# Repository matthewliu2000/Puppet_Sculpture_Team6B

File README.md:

# Puppet_Sculpture_Team6B
github repository for Team 6B ECE3872 Sculpture Project

# Hardware
1. PCB Schematic (shield_schematic.sh)
2. shield_schematic.brd
3. PCB Eagle Files: ECE3872A_6B_PCB_Shield.zip

# Software
1. HW & SW Component Level Tests: in test_code Folder
2. Draft Simulation Code: ArduinoSimulationCode.ino
3. Final Simulation Code: ArduinoSimulationCodeV2.ino

# Final Demonstration: 
https://youtu.be/2q0zukCzHsM

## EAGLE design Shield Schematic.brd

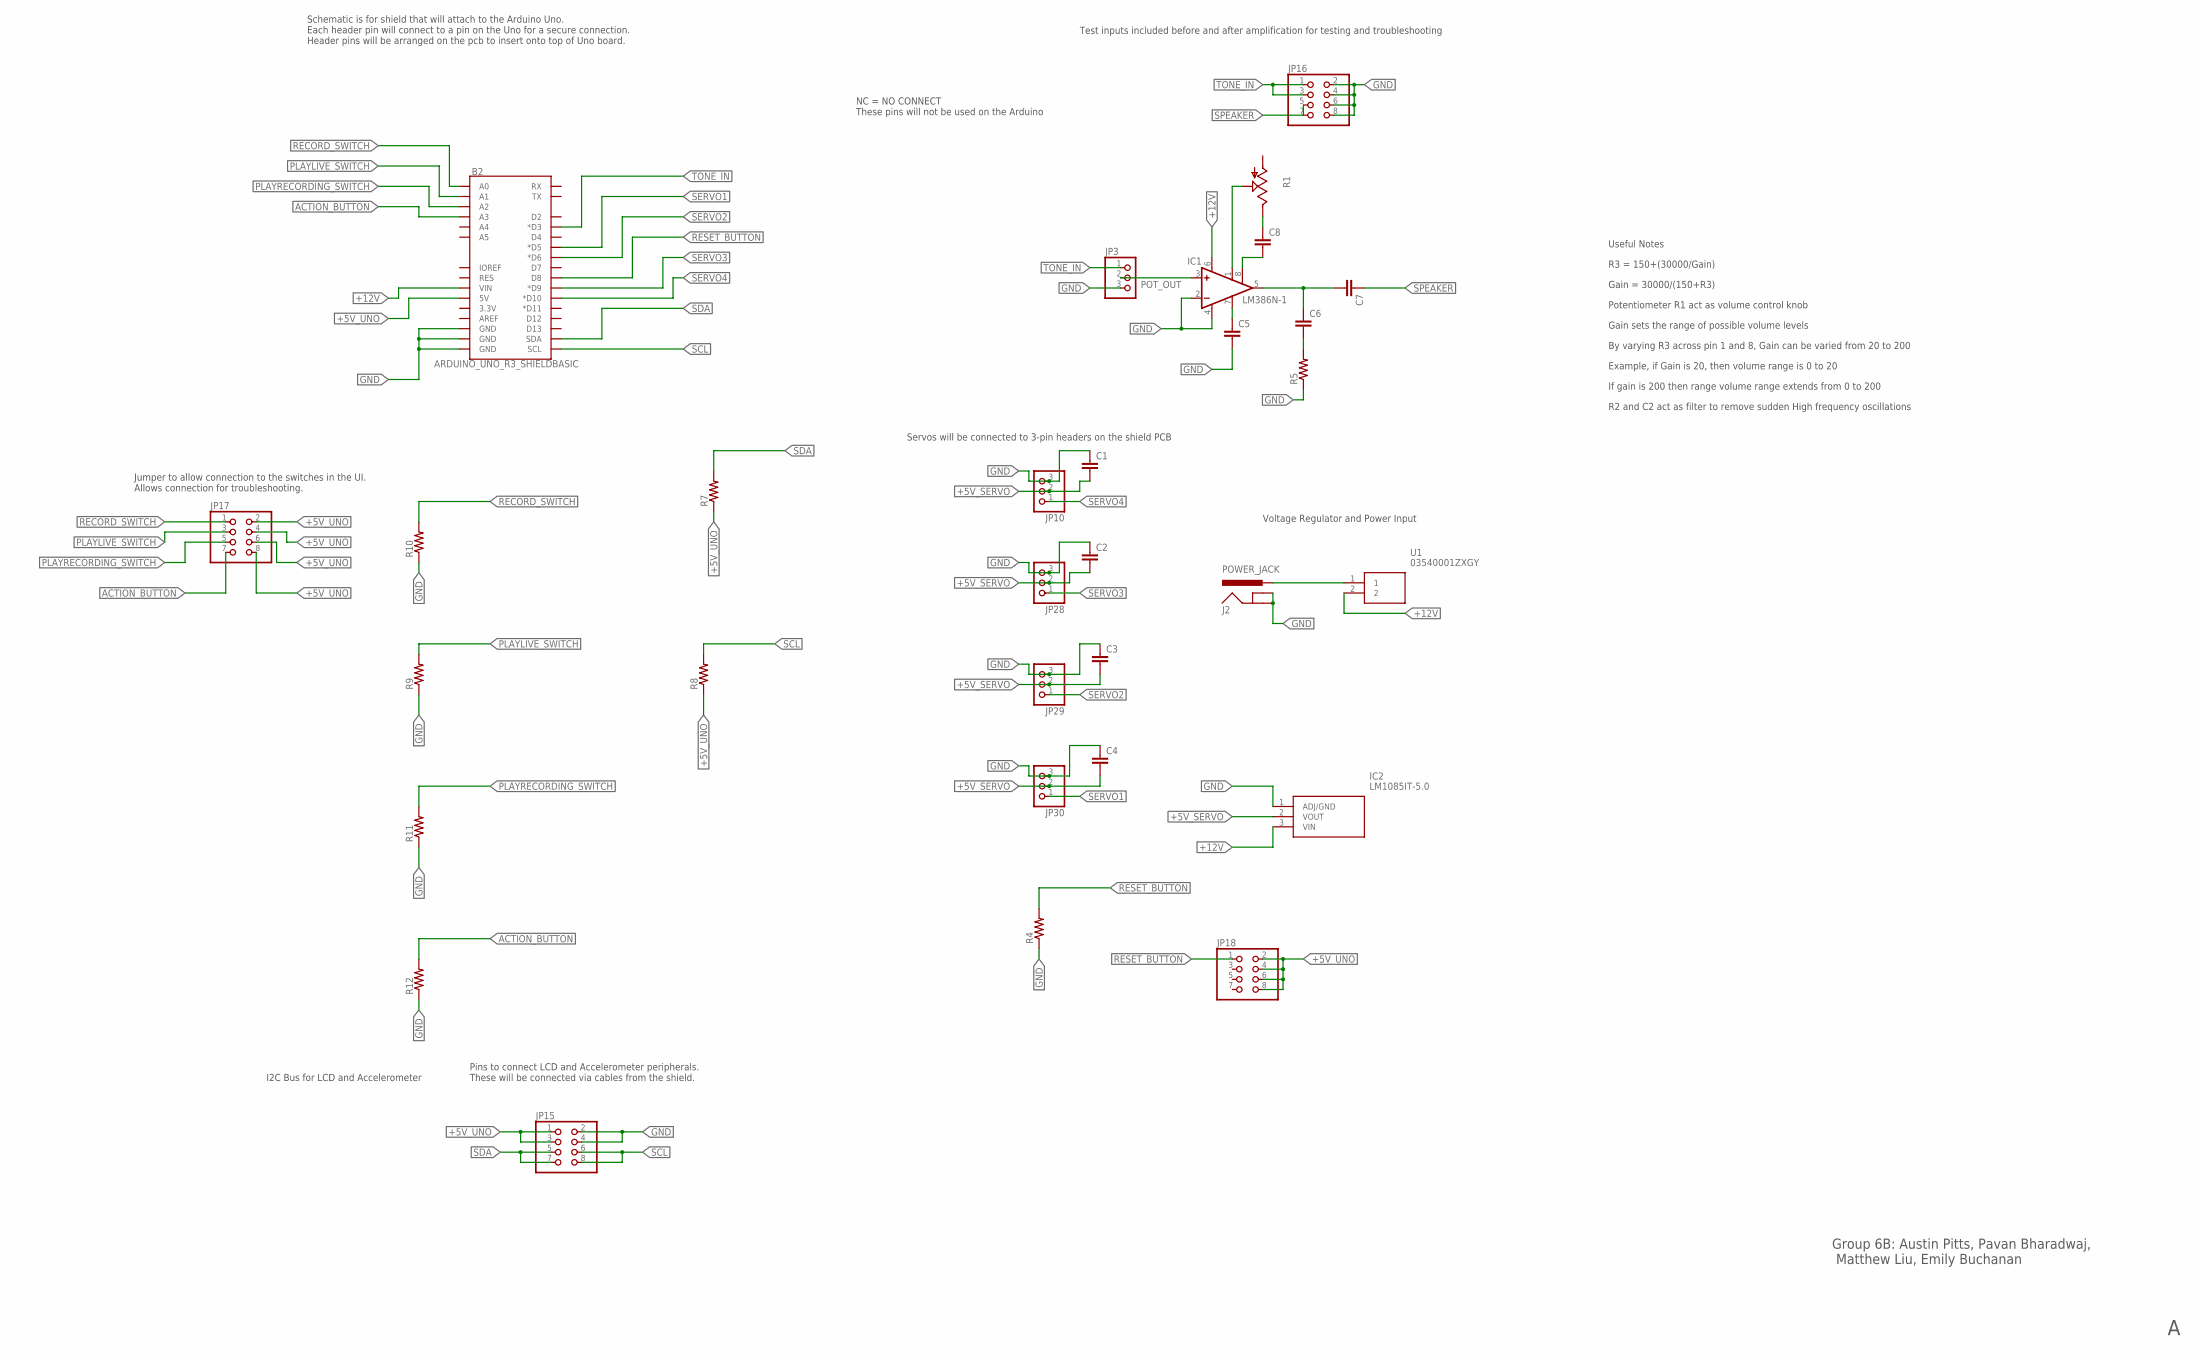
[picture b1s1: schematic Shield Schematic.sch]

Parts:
B2: ARDUINO_UNO_R3_SHIELDBASIC; UNO_R3_SHIELD
C1, C2, C3, C4, C5, C6, C7, C8: C2,5-3; C2.5-3
IC1: LM386N-1; DIL08
IC2: LM1085IT-5.0; TO254P470X1016X2222-3P
J2: POWER_JACK; POWER_JACK_PTH
JP3, JP10, JP28, JP29, JP30: PINHD-1X3; 1X03
JP15, JP16, JP17, JP18: PINHD-2X4; 2X04
R1: TRIM_US-B25P; B25P
R4, R5, R7, R8, R9, R10, R11, R12: R-US_0207/7; 0207/7
U1: 03540001ZXGY; 03540101ZXGY

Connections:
+5V_SERVO: C1.2, C2.2, C3.2, C4.2, IC2.2 (VOUT), JP10.2, JP28.2, JP29.2, JP30.2
+5V_UNO: B2.5V, JP15.1, JP15.3, JP17.2, JP17.4, JP17.6, JP17.8, JP18.2, JP18.4, JP18.6, JP18.8, R7.1, R8.1
+12V: B2.VIN, IC1.6 (VS), IC2.3 (VIN), U1.2
ACTION_BUTTON: B2.A3, JP17.7, R12.2
GND: B2.GND@0 (GND), B2.GND@1 (GND), B2.GND@2 (GND), C1.1, C2.1, C3.1, C4.1, C5.2, IC1.2 (-IN), IC1.4 (GND), IC2.1 (ADJ/GND), J2.GND, J2.GNDBREAK, JP3.3, JP10.3, JP15.2, JP15.4, JP16.2, JP16.4, JP16.6, JP16.8, JP28.3, JP29.3, JP30.3, R4.1, R5.1, R9.1, R10.1, R11.1, R12.1
unnamed: J2.PWR, U1.1
unnamed: C6.1, C7.2, IC1.5 (OUT)
unnamed: C6.2, R5.2
unnamed: C5.1, IC1.7 (BYPASS)
unnamed: C8.2, IC1.8 (GAIN)
unnamed: C8.1, R1.E
unnamed: IC1.1 (GAIN), R1.S
PLAYLIVE_SWITCH: B2.A1, JP17.3, R9.2
PLAYRECORDING_SWITCH: B2.A2, JP17.5, R11.2
POT_OUT: IC1.3 (+IN), JP3.2
RECORD_SWITCH: B2.A0, JP17.1, R10.2
RESET_BUTTON: B2.D8, JP18.1, R4.2
SCL: B2.SCL, JP15.6, JP15.8, R8.2
SDA: B2.SDA, JP15.5, JP15.7, R7.2
SERVO1: B2.D5 (*D5), JP30.1
SERVO2: B2.D6 (*D6), JP29.1
SERVO3: B2.D9 (*D9), JP28.1
SERVO4: B2.D10 (*D10), JP10.1
SPEAKER: C7.1, JP16.5, JP16.7
TONE_IN: B2.D3 (*D3), JP3.1, JP16.1, JP16.3

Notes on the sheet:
Potentiometer R1 act as volume control knob
R2 and C2 act as filter to remove sudden High frequency oscillations
Gain sets the range of possible volume levels
Gain = 30000/(150+R3)
R3 = 150+(30000/Gain)
Useful Notes
By varying R3 across pin 1 and 8, Gain can be varied from 20 to 200
Example, if Gain is 20, then volume range is 0 to 20
If gain is 200 then range volume range extends from 0 to 200
I2C Bus for LCD and Accelerometer
Schematic is for shield that will attach to the Arduino Uno. Each header pin will connect to a pin on the Uno for a secure connection. Header pins will be arranged on the pcb to insert onto top of Uno board.
Servos will be connected to 3-pin headers on the shield PCB
Pins to connect LCD and Accelerometer peripherals. These will be connected via cables from the shield.
NC = NO CONNECT These pins will not be used on the Arduino
Voltage Regulator and Power Input
Test inputs included before and after amplification for testing and troubleshooting
Group 6B: Austin Pitts, Pavan Bharadwaj, Matthew Liu, Emily Buchanan
Jumper to allow connection to the switches in the UI. Allows connection for troubleshooting.

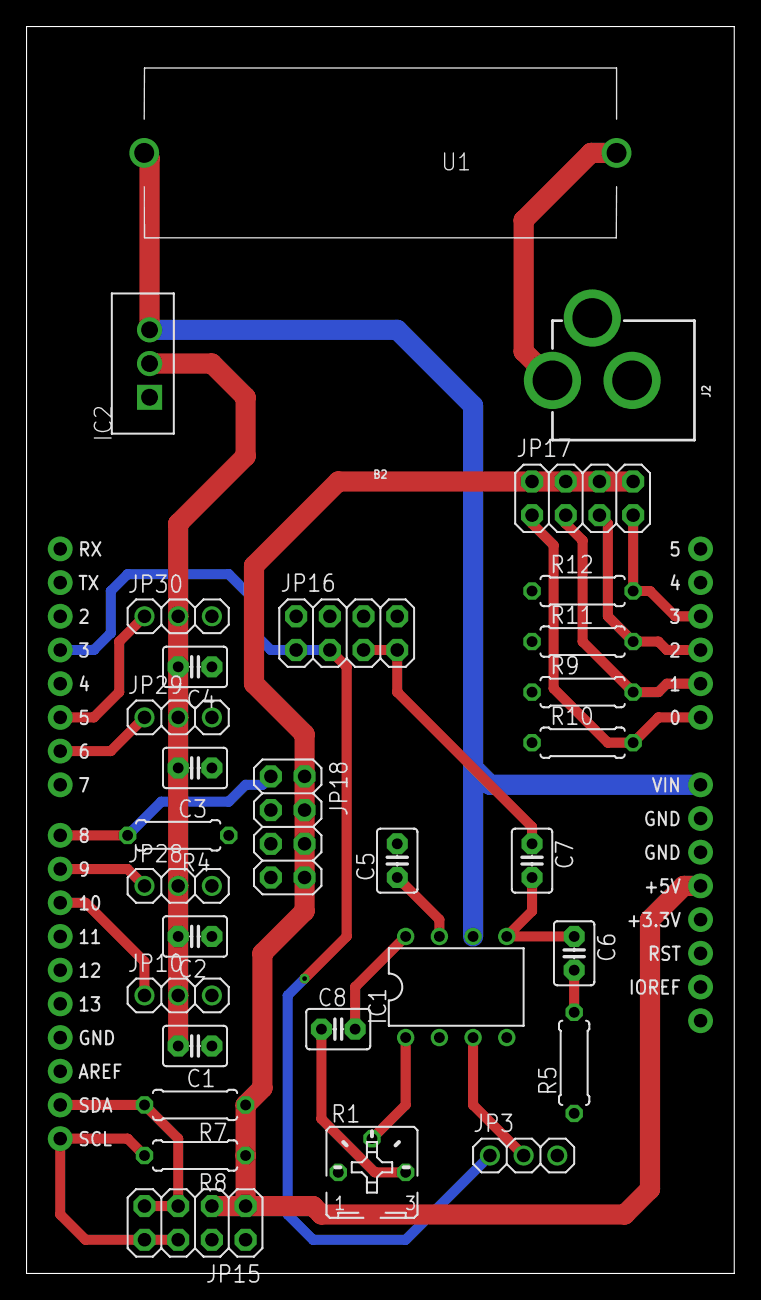
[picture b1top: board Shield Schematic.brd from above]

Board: 2 copper layers, 53.3 x 94.0 mm, 31 parts (0 on the bottom side), 25 nets.

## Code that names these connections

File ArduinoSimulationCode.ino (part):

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  for (int i = 14; i <= 18; i++) {
    pinMode(i, INPUT);
  }
  //Speaker and Servo pin modes
  pinMode(speakerPin,OUTPUT);
  pinMode(servo1Pin,OUTPUT);
  pinMode(servo2Pin,OUTPUT);
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  canPlayLive = false;
  
//Attach Servo Motor Objects to pins
  servo1.attach(servo1Pin);
  servo2.attach(servo2Pin);
  servo3.attach(servo3Pin);
  servo4.attach(servo4Pin);

//Set input recording array to empty (all zeros)
for(int i = 0;i<RecordingLength;i++){
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
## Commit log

2020-10-04 Initial Shield PCB Schematic (Eagle)
2020-10-23 Add files via upload
    Testing interface b/n LCD and accelerometer.
    Description:
    Outputs accelerometer measurement values to LCD and serial monitor
2020-11-07 Rename accelerometer_lcd_arduino_test.ino to test_code/accelerometer_lcd_arduino_test.ino
2020-11-07 Rename acceldemo.ino to test_code/acceldemo.ino
2020-11-07 Rename puppet_hw_integ_test.ino to test_code/puppet_hw_integ_test.ino
2020-11-07 Rename ServoTest.ino to test_code/ServoTest.ino
2020-11-07 Rename Shield Schematic.brd to HW_Files/Shield Schematic.brd
2020-11-07 Rename Shield Schematic.sch to HW_Files_Shield Schematic.sch
2020-11-07 Rename HW_Files_Shield Schematic.sch to HW_Files/Shield Schematic.sch

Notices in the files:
parts and their libraries:
SparkFun-Boards: Licensing: Creative Commons ShareAlike 4.0 International - https://creativecommons.org/licenses/by-sa/4.0
